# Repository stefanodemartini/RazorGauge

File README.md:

# RazorGauge

RazorGauge is a line-diameter measurement and fly-line design project. This repository contains
the firmware, Windows desktop application, shared physics library, CLI, and the hardware design
files.

## Repository map

| Path | Purpose |
|---|---|
| `master/` | Active ESP32 master firmware (0.4.25-RB2, caliper-based) |
| `slave/` | Active ESP32-classic motor controller firmware (0.6.8, Wi-Fi/RX2 diagnostics) |
| `master_razorgauge/` | Preliminary optical RazorGauge master (1.0.4-alpha) |
| `gauge_esp32/`, `gauge_esp32s3/`, `encoder_test/` | Bench and diagnostic firmware |
| `app/` | Windows WPF desktop application |
| `FlyLinePhysics/` | Shared line-physics and `.flp` serialization library |
| `FlyLinePhysics.Tests/` | Unit tests for the shared library |
| `cli/` | `flyline` command-line design and analysis tool |
| `cad/`, `integrazione_profiler/`, `piastra_alluminio/` | Mechanical CAD and integration design |
| `scheda/`, `scheda_smd/` | RazorBoard KiCad projects |
| `strumenti/` | Build, simulation, and verification scripts |

Generated outputs (such as mesh files, renders, PDFs, and build products) are generally excluded
from version control; the corresponding source files and scripts are kept in the repository.

## Where to start

- [FIRMWARE.md](./FIRMWARE.md): canonical sketches, active versions, boards, and firmware notes.
- [MANUALE.md](./MANUALE.md): application workflow and user-facing behavior.
- [STATO_PROGETTO.md](./STATO_PROGETTO.md): authoritative hardware decisions and current project status.
- [CONTEXT.md](./CONTEXT.md): software/repository context.
- [app/README.md](./app/README.md): desktop application overview.

## Build and test the .NET projects

From the repository root:

```powershell
dotnet build app\app.sln
dotnet test FlyLinePhysics.Tests\FlyLinePhysics.Tests.csproj
dotnet build cli\FlyLineCli.csproj
```

Run the desktop app with `dotnet run --project app\DiametroLineaDesktop.csproj`. The CLI project
is Windows-targeted because it currently references the WPF application for shared design and
export services.

## Arduino firmware

Build and flash each sketch for its matching board using Arduino IDE or `arduino-cli`. The active
motor slave targets the classic ESP32; do not select ESP32-S3 for `slave/slave.ino`. See
[FIRMWARE.md](./FIRMWARE.md) for the current board/version matrix and flash guidance.

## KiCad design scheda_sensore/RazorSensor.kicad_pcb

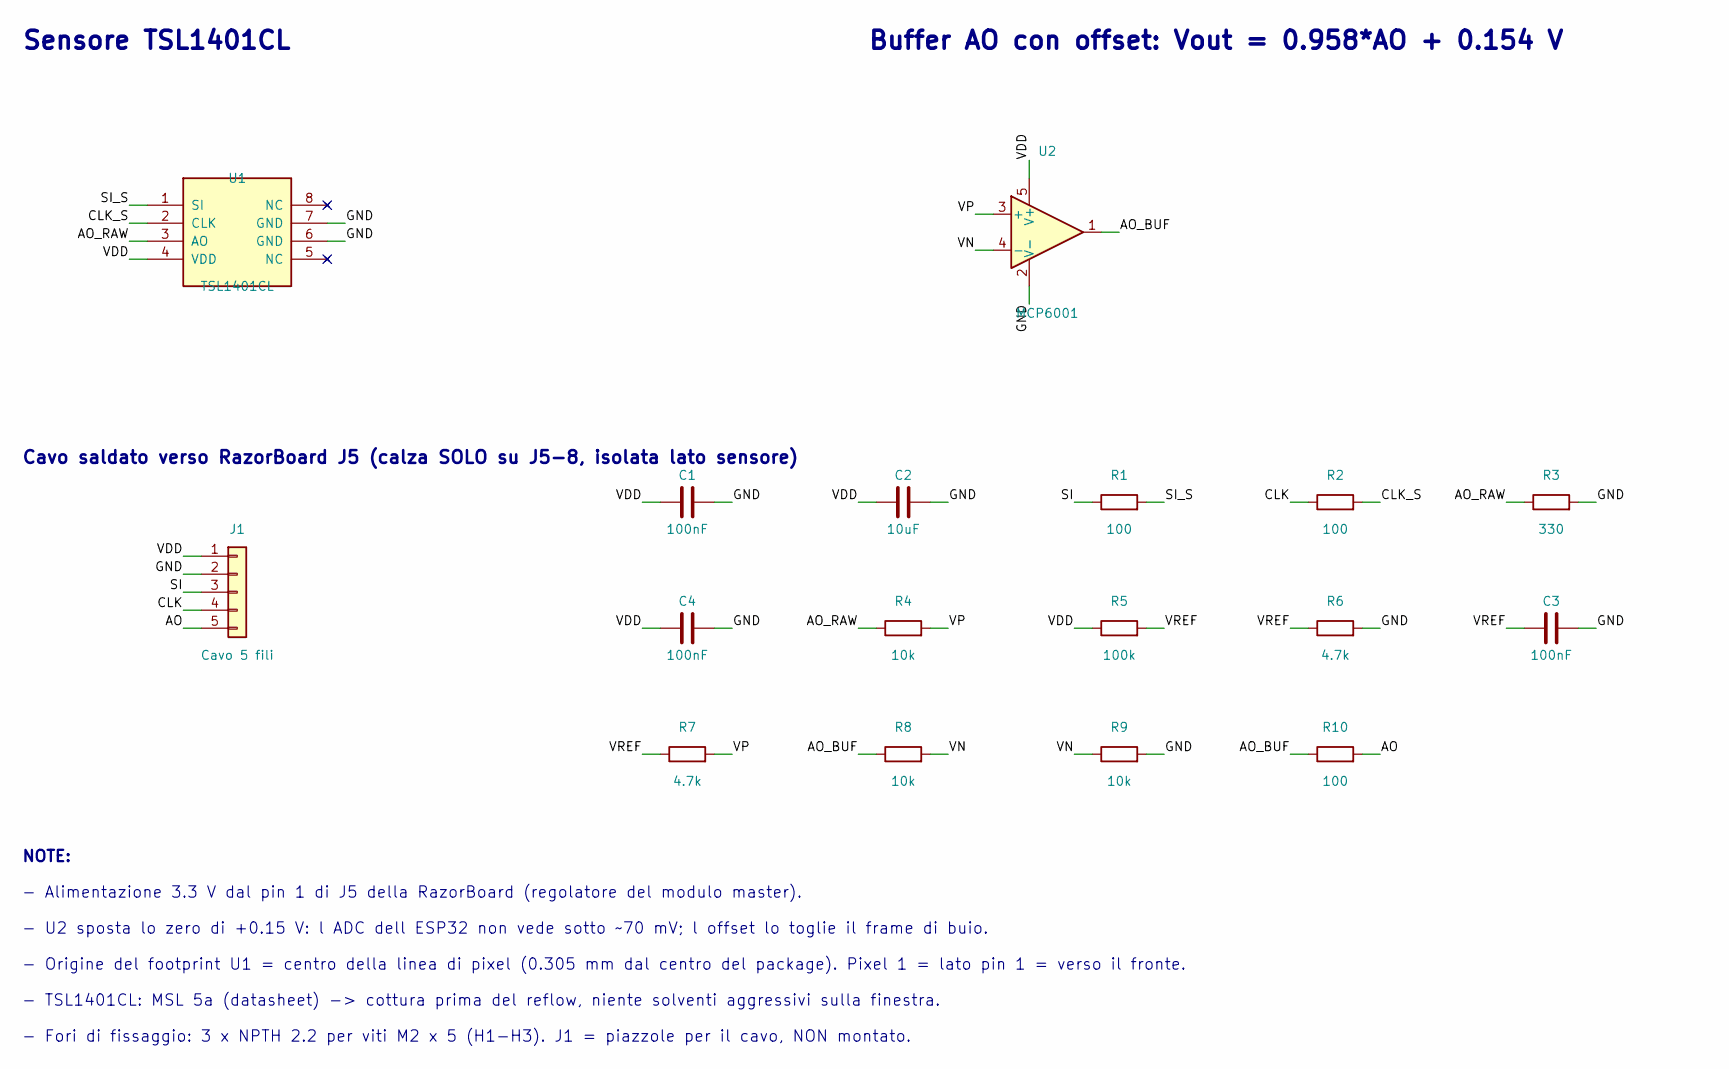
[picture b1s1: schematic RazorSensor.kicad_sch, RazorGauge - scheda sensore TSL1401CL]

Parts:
C1, C3, C4: 100nF; C_0603_1608Metric; MPN CC0603KRX7R9BB104 50V; LCSC C14663
C2: 10uF; C_0805_2012Metric; MPN CL21A106KAYNNNE 25V; LCSC C15850
J1: Cavo 5 fili; PinHeader_1x05_P2.00mm_Vertical; MPN piazzole per saldare il cavo: 1 3V3 / 2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
R1, R2, R10: 100; R_0603_1608Metric; MPN 0603WAF1000T5E; LCSC C22775
R3: 330; R_0603_1608Metric; MPN 0603WAF3300T5E; LCSC C23138
R4, R8, R9: 10k; R_0603_1608Metric; MPN 0603WAF1002T5E; LCSC C25804
R5: 100k; R_0603_1608Metric; MPN 0603WAF1003T5E; LCSC C25803
R6, R7: 4.7k; R_0603_1608Metric; MPN 0603WAF4701T5E; LCSC C23162
U1: TSL1401CL; TSL1401CL_ams_CL; MPN ams TSL1401CL (128x1, package CL, MSL 5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; LCSC C2802316
U2: MCP6001; SOT-23-5; MPN Microchip MCP6001T-I/OT (rail-to-rail i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; LCSC C116490

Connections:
AO: J1.5, R10.2
AO_BUF: R8.1, R10.1, U2.1
AO_RAW: R3.1, R4.1, U1.3 (AO)
CLK: J1.4, R2.1
CLK_S: R2.2, U1.2 (CLK)
GND: C1.2, C2.2, C3.2, C4.2, J1.2, R3.2, R6.2, R9.2, U1.6 (GND), U1.7 (GND), U2.2 (V-)
SI: J1.3, R1.1
SI_S: R1.2, U1.1 (SI)
VDD: C1.1, C2.1, C4.1, J1.1, R5.1, U1.4 (VDD), U2.5 (V+)
VN: R8.2, R9.1, U2.4 (-)
VP: R4.2, R7.2, U2.3 (+)
VREF: C3.1, R5.2, R6.1, R7.1

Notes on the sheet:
Sensore TSL1401CL
Cavo saldato verso RazorBoard J5 (calza SOLO su J5-8, isolata lato sensore)
Buffer AO con offset: Vout = 0.958*AO + 0.154 V
NOTE:
- Alimentazione 3.3 V dal pin 1 di J5 della RazorBoard (regolatore del modulo master).
- U2 sposta lo zero di +0.15 V: l ADC dell ESP32 non vede sotto ~70 mV; l offset lo toglie il frame di buio.
- Origine del footprint U1 = centro della linea di pixel (0.305 mm dal centro del package). Pixel 1 = lato pin 1 = verso il fronte.
- TSL1401CL: MSL 5a (datasheet) -> cottura prima del reflow, niente solventi aggressivi sulla finestra.
- Fori di fissaggio: 3 x NPTH 2.2 per viti M2 x 5 (H1-H3). J1 = piazzole per il cavo, NON montato.

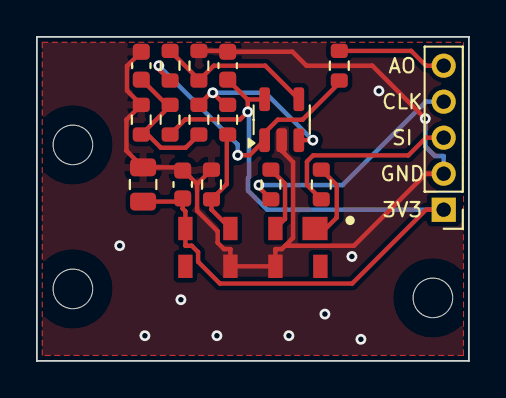
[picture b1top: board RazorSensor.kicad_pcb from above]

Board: 2 copper layers, 24.0 x 18.0 mm, 20 parts (0 on the bottom side), 12 nets.

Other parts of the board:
H1, H2, H3: M2; MountingHole_2.2mm_M2

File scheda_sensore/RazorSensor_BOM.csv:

Rif;Valore;Footprint;Codice / note;LCSC
U1;TSL1401CL;TSL1401CL_ams_CL;ams TSL1401CL (128x1, package CL, MSL 5a da datasheet);C2802316
C1;100nF;C_0603_1608Metric;CC0603KRX7R9BB104 50V;C14663
C2;10uF;C_0805_2012Metric;CL21A106KAYNNNE 25V;C15850
R1;100;R_0603_1608Metric;0603WAF1000T5E;C22775
R2;100;R_0603_1608Metric;0603WAF1000T5E;C22775
R3;330;R_0603_1608Metric;0603WAF3300T5E;C23138
U2;MCP6001;SOT-23-5;Microchip MCP6001T-I/OT (rail-to-rail in/out, 1 MHz, 0.6 V/us) - NON LMV321/MCP6001R/MCP6001U;C116490
C4;100nF;C_0603_1608Metric;CC0603KRX7R9BB104 50V;C14663
R4;10k;R_0603_1608Metric;0603WAF1002T5E;C25804
R5;100k;R_0603_1608Metric;0603WAF1003T5E;C25803
R6;4.7k;R_0603_1608Metric;0603WAF4701T5E;C23162
C3;100nF;C_0603_1608Metric;CC0603KRX7R9BB104 50V;C14663
R7;4.7k;R_0603_1608Metric;0603WAF4701T5E;C23162
R8;10k;R_0603_1608Metric;0603WAF1002T5E;C25804
R9;10k;R_0603_1608Metric;0603WAF1002T5E;C25804
R10;100;R_0603_1608Metric;0603WAF1000T5E;C22775
J1;Cavo 5 fili;PinHeader_1x05_P2.00mm_Vertical;"piazzole per saldare il cavo: 1 3V3 / 2 GND / 3 SI / 4 CLK / 5 AO (= J5 pin 1-5; calza solo su J5-8) - NON MONTARE";

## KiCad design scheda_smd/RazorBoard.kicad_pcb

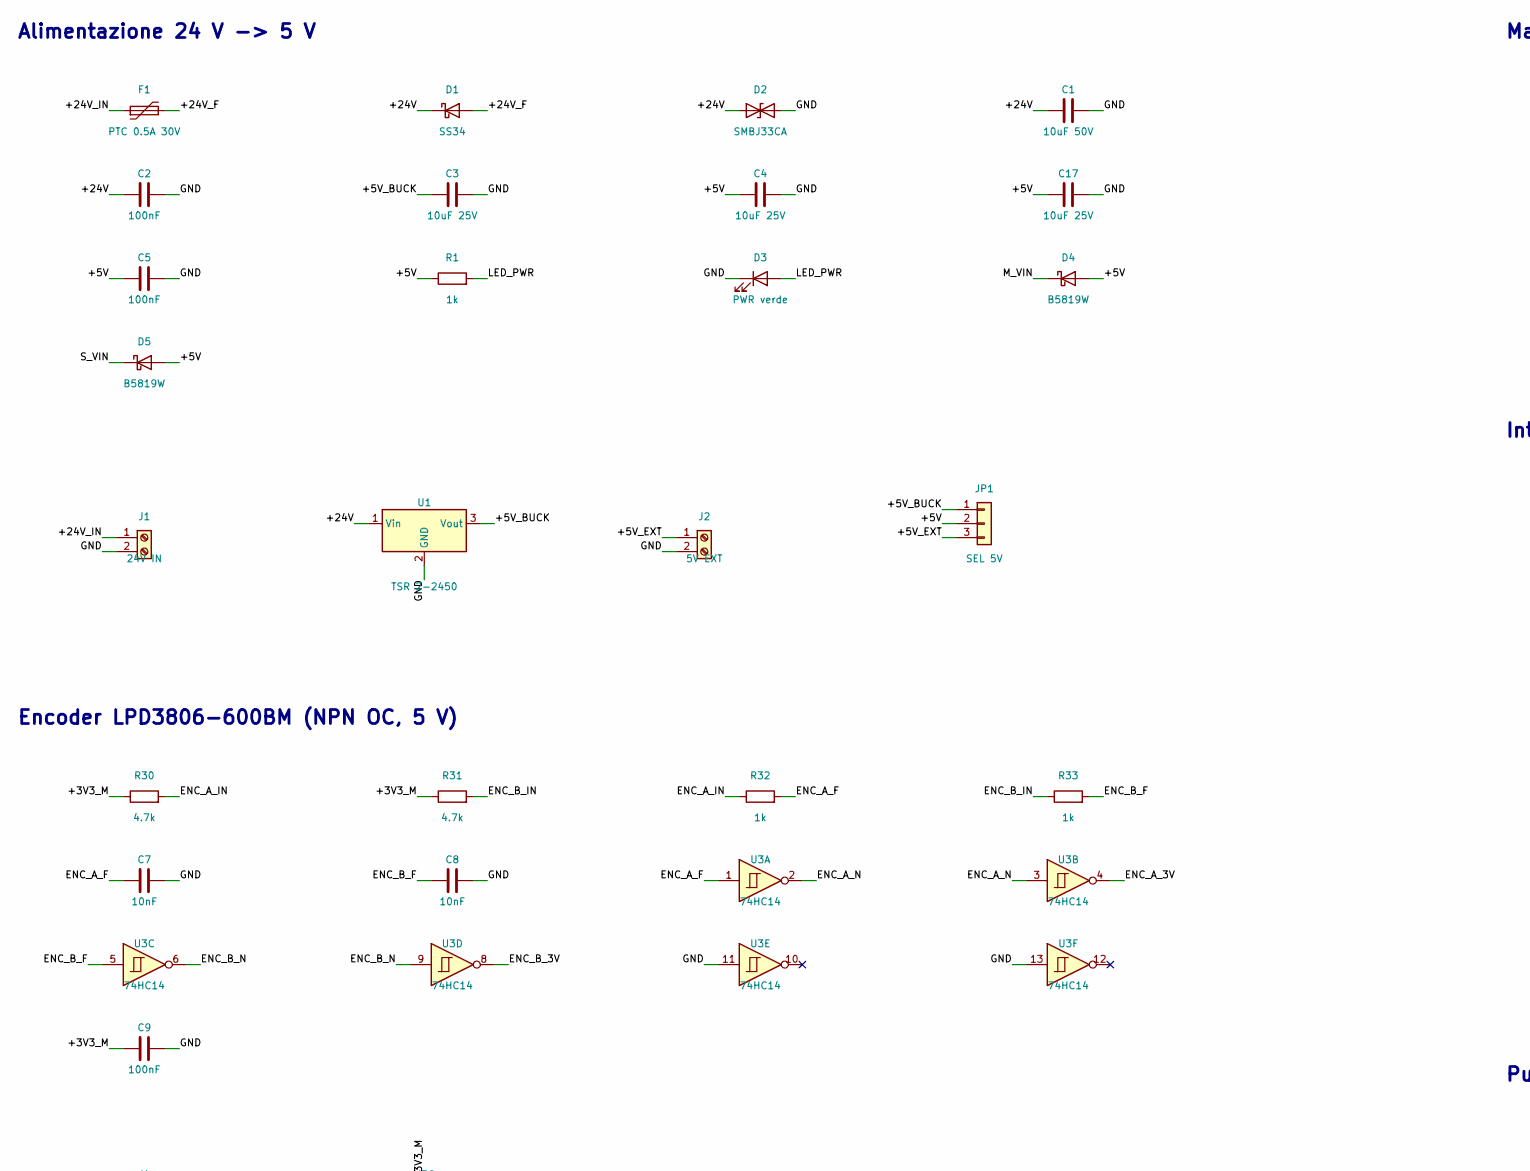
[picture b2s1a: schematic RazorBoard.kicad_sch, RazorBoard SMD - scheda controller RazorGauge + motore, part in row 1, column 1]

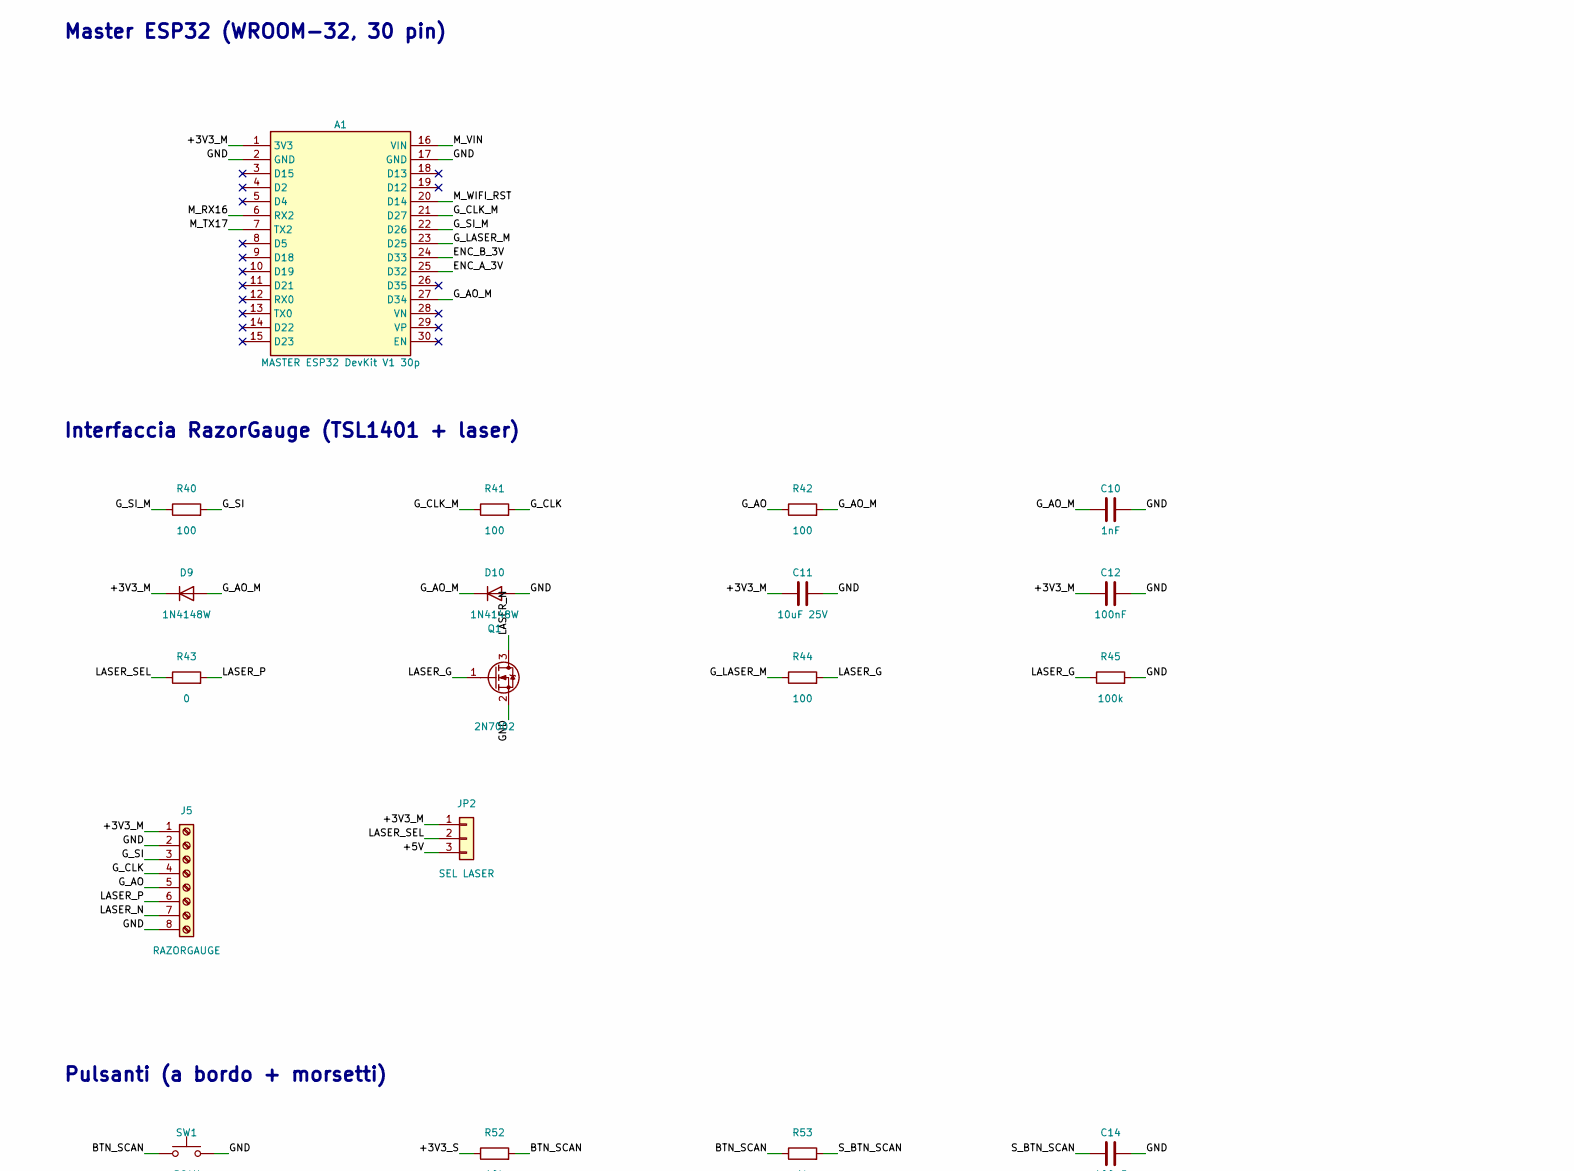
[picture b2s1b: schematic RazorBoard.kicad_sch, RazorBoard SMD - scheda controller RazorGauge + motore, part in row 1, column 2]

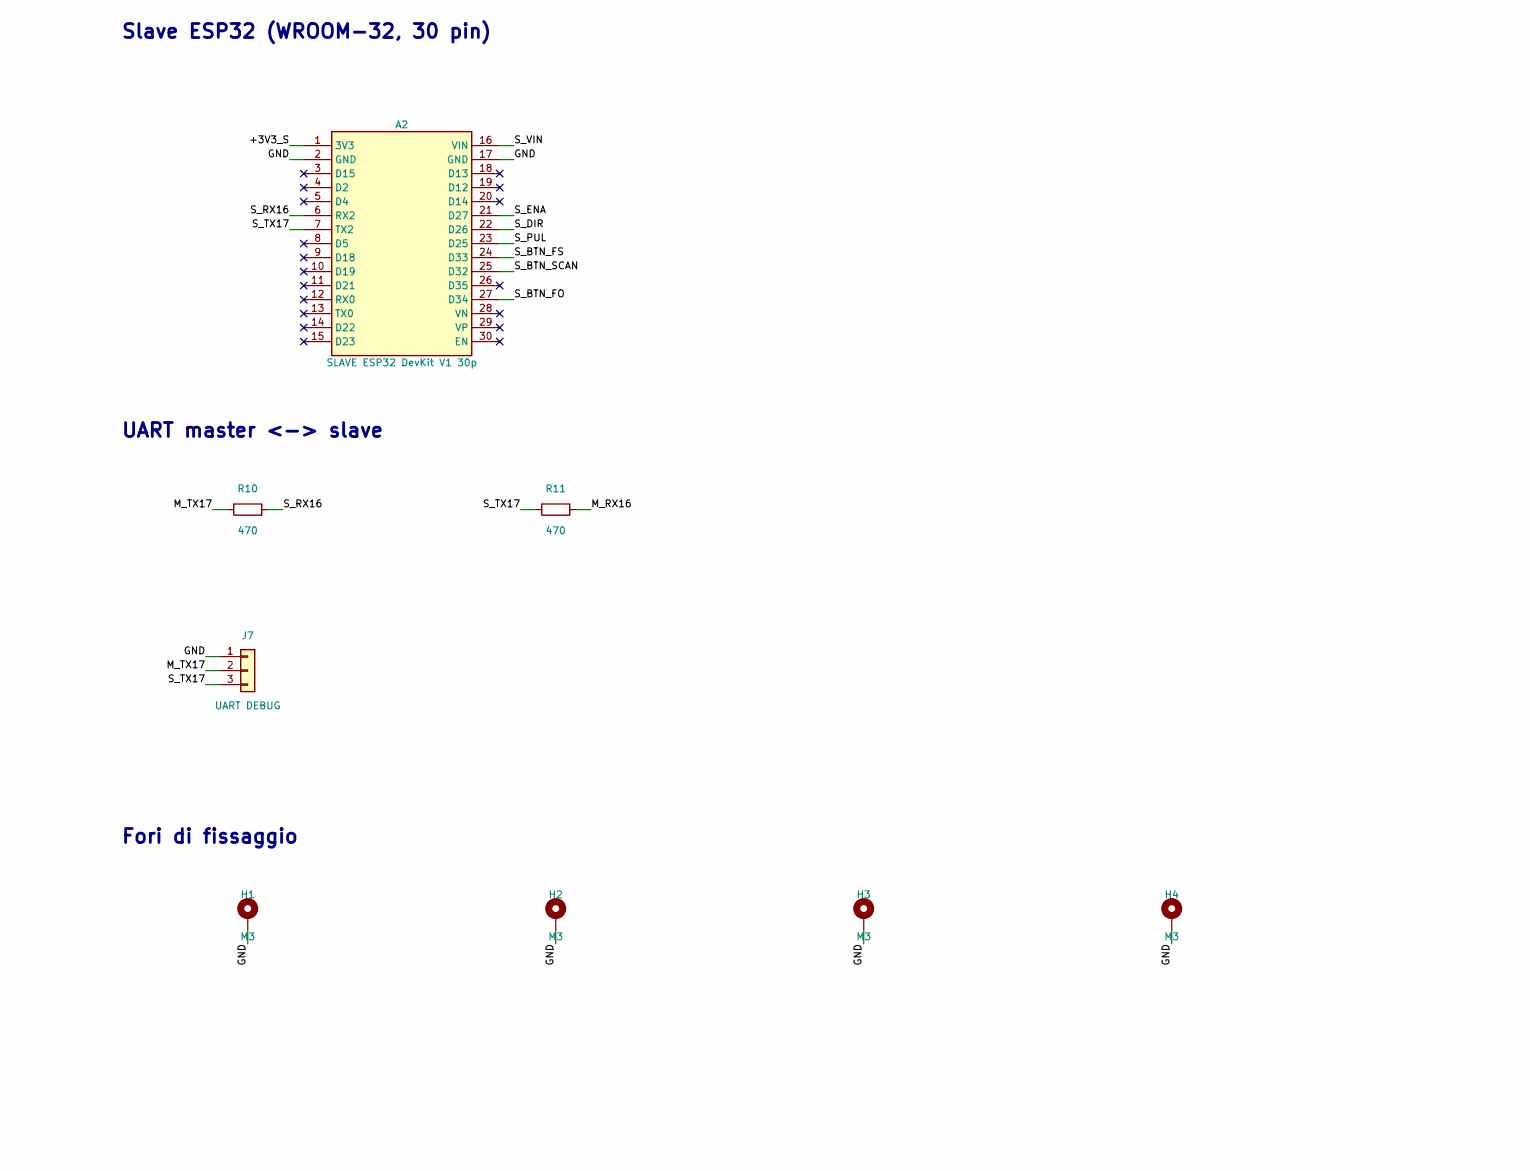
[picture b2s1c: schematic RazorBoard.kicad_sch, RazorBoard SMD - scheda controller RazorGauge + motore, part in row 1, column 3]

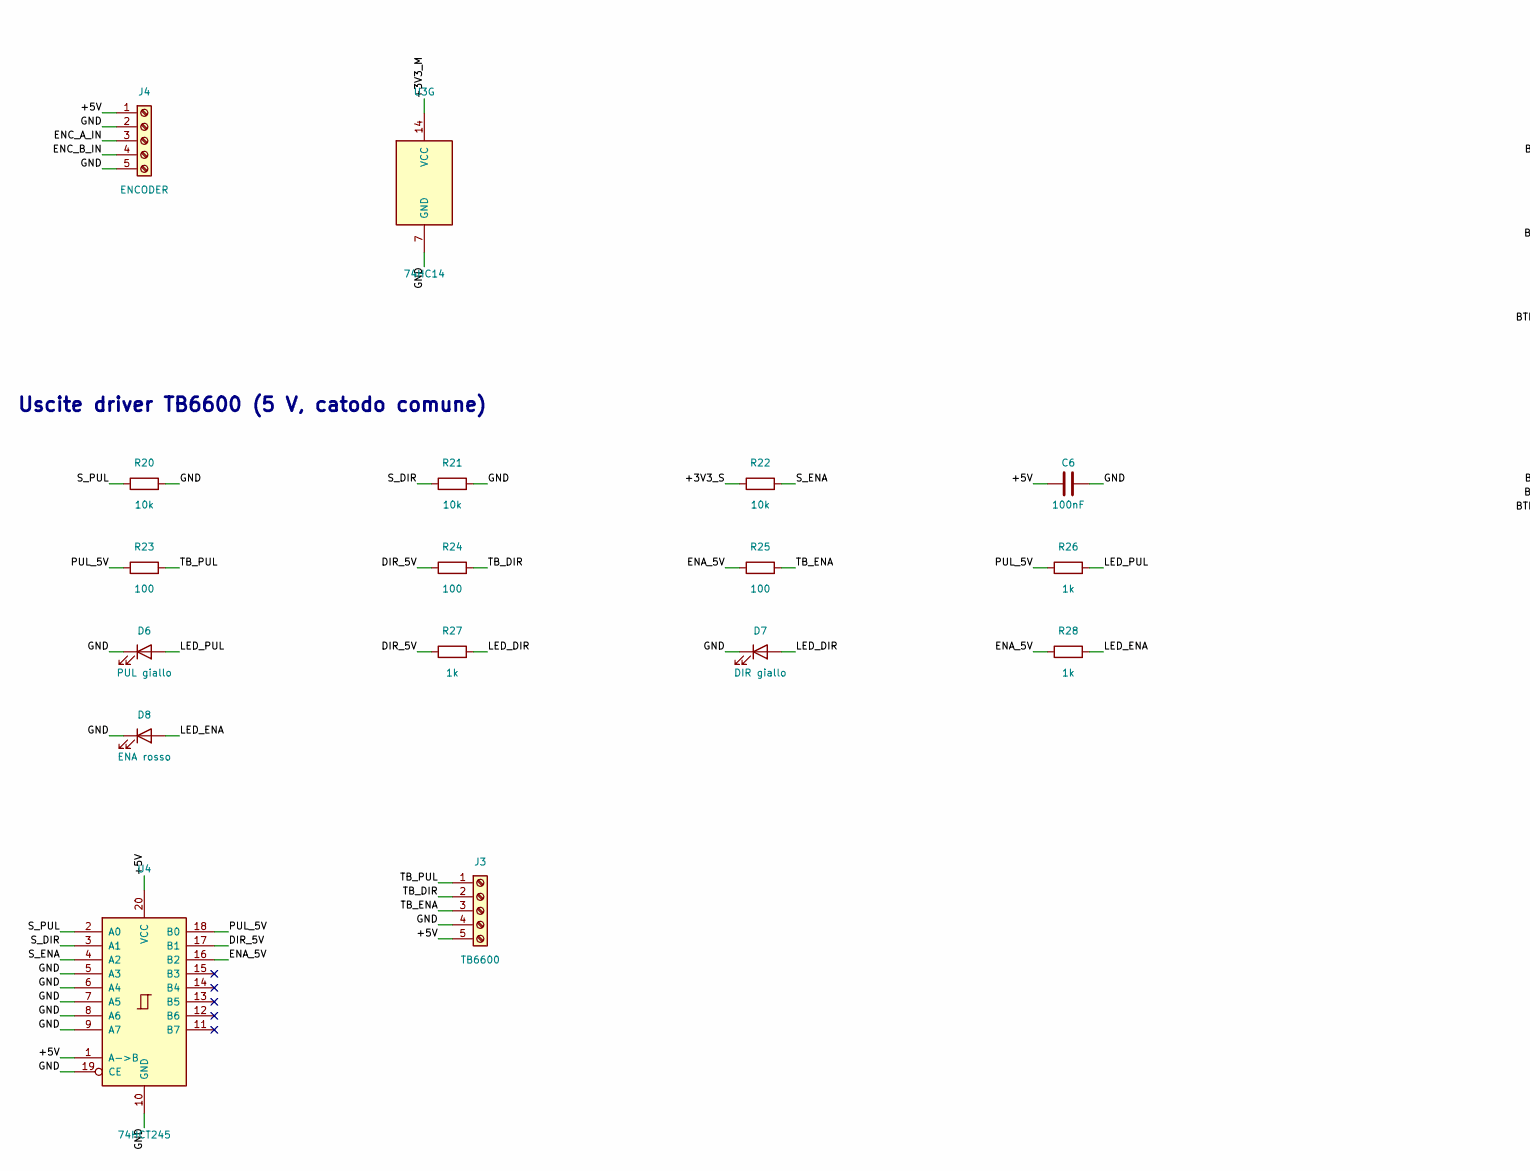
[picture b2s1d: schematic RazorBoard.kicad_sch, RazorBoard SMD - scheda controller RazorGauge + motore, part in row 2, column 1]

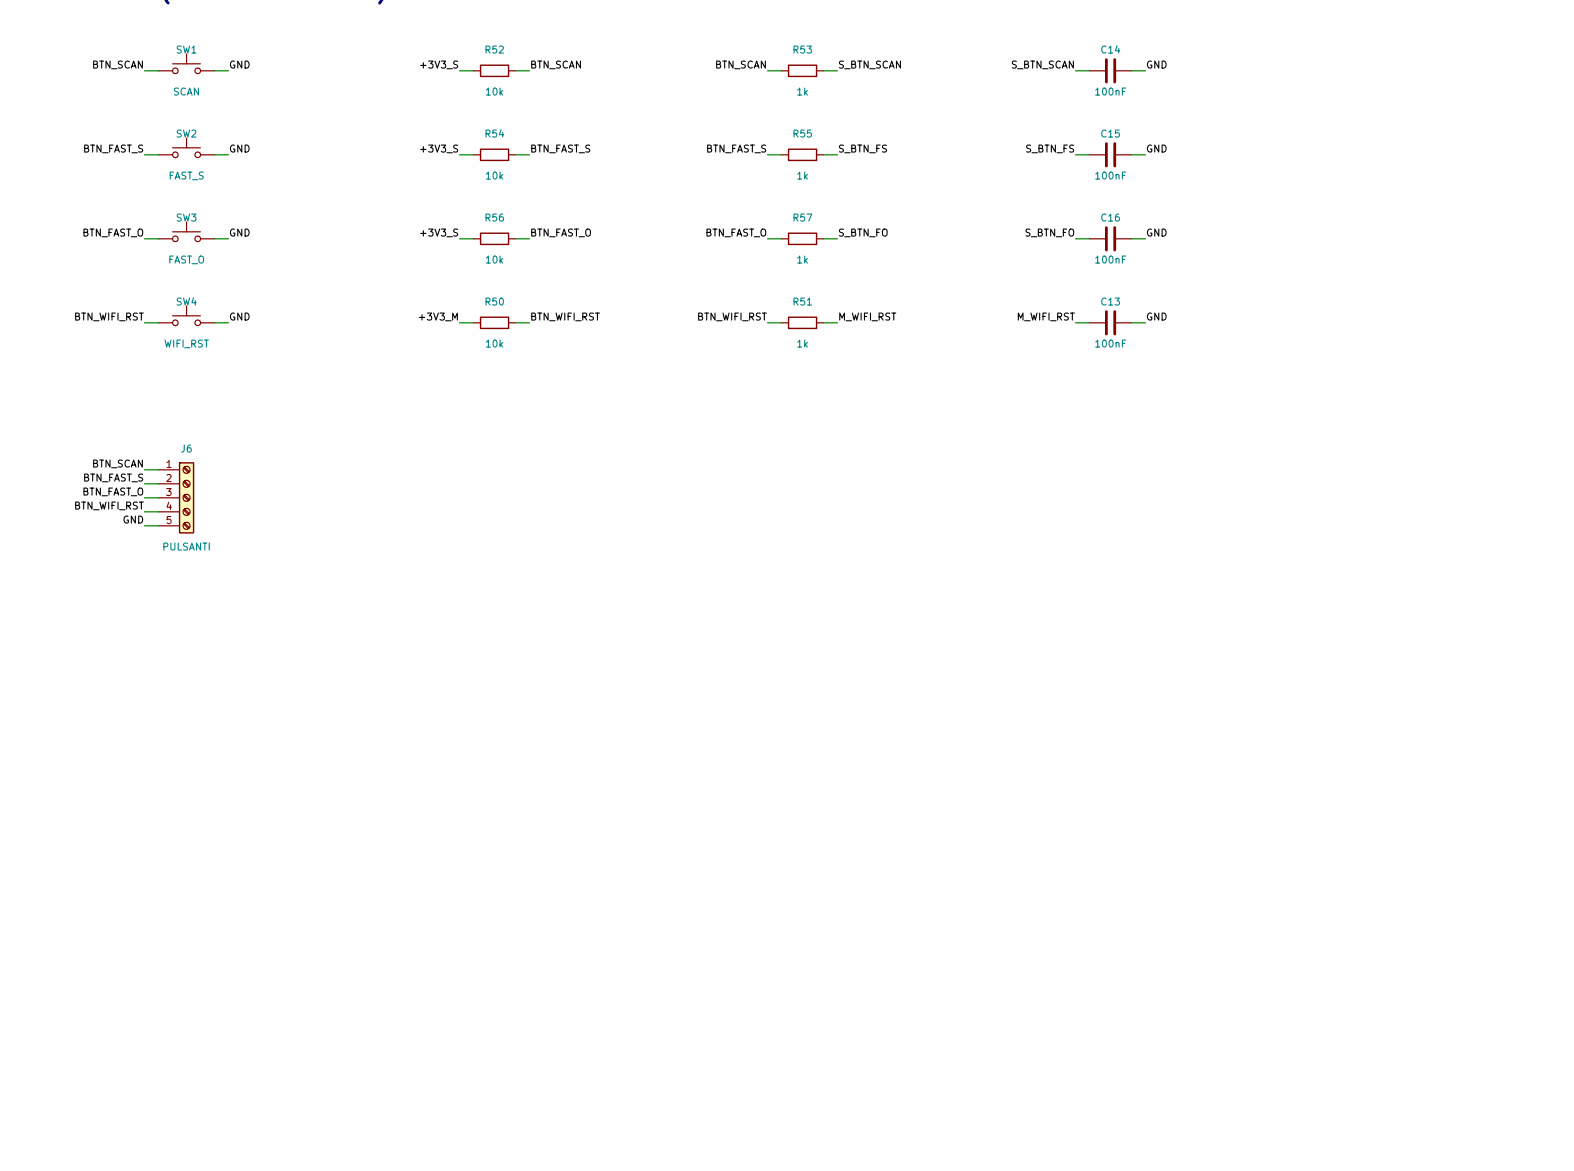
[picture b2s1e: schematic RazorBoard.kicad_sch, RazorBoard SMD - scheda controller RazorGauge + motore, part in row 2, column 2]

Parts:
A1: MASTER ESP32 DevKit V1 30p; ESP32_DevKitV1_30p_W25.4; MPN 2x zoccolo femmina 1x15 passo 2.54, fil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
A2: SLAVE ESP32 DevKit V1 30p; ESP32_DevKitV1_30p_W25.4; MPN 2x zoccolo femmina 1x15 passo 2.54, fil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
C1: 10uF 50V; C_1206_3216Metric; MPN CL31A106KBHNNNE; LCSC C13585
C2, C5, C6, C9, C12, C13, C14, C15, C16: 100nF; C_0603_1608Metric; MPN CC0603KRX7R9BB104 50V; LCSC C14663
C3, C4, C11, C17: 10uF 25V; C_0805_2012Metric; MPN CL21A106KAYNNNE; LCSC C15850
C7, C8: 10nF; C_0603_1608Metric; MPN 0603B103K500NT 50V; LCSC C57112
C10: 1nF; C_0603_1608Metric; MPN CL10B102KB8NNNC 50V; LCSC C1588
D1: SS34; D_SMA; MPN SS34 3A 40V; LCSC C8678
D2: SMBJ33CA; D_SMB; MPN SMBJ33CA; LCSC C492017
D3: PWR verde; LED_0603_1608Metric; MPN KT-0603G; LCSC C12624
D4: B5819W; D_SOD-123; MPN B5819W SL (blocca ritorno da USB master); LCSC C8598
D5: B5819W; D_SOD-123; MPN B5819W SL (blocca ritorno da USB slave); LCSC C8598
D6: PUL giallo; LED_0603_1608Metric; MPN KT-0603Y; LCSC C2287
D7: DIR giallo; LED_0603_1608Metric; MPN KT-0603Y; LCSC C2287
D8: ENA rosso; LED_0603_1608Metric; MPN KT-0603R; LCSC C2286
D9, D10: 1N4148W; D_SOD-123; MPN 1N4148W; LCSC C81598
F1: PTC 0.5A 30V; Fuse_1812_4532Metric; MPN SMD1812P050TF/30 (hold 0.5A, trip 1A); LCSC C12559
H1, H2, H3, H4: M3; MountingHole_3.2mm_M3_Pad
J1: 24V IN; TerminalBlock_Phoenix_MKDS-1,5-2-5.08_1x02_P5.08mm_Horizont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
J2: 5V EXT; TerminalBlock_Phoenix_MKDS-1,5-2-5.08_1x02_P5.08mm_Horizont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
J3: TB6600; TerminalBlock_Phoenix_MKDS-1,5-5-5.08_1x05_P5.08mm_Horizont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; MPN PUL->PUL+, DIR->DIR+, ENA->ENA+, GND->P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
J4: ENCODER; TerminalBlock_Phoenix_MKDS-1,5-5-5.08_1x05_P5.08mm_Horizont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; MPN rosso +5V, nero GND, verde A, bianco B,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
J5: RAZORGAUGE; TerminalBlock_Phoenix_MKDS-1,5-8-5.08_1x08_P5.08mm_Horizont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; MPN cavo schermato max 50 cm, calza al pin 8
J6: PULSANTI; TerminalBlock_Phoenix_MKDS-1,5-5-5.08_1x05_P5.08mm_Horizont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
J7: UART DEBUG; PinHeader_1x03_P2.54mm_Vertical
JP1: SEL 5V; PinHeader_1x03_P2.54mm_Vertical; MPN Header 3 pin + jumper (1-2 = convertito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
JP2: SEL LASER; PinHeader_1x03_P2.54mm_Vertical; MPN Header 3 pin + jumper (1-2 = laser a 3.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
Q1: 2N7002; SOT-23; MPN 2N7002 (60V 115mA); LCSC C8545
R1, R26, R27, R28, R32, R33, R51, R53, R55, R57: 1k; R_0603_1608Metric; MPN 0603WAF1001T5E; LCSC C21190
R10, R11: 470; R_0603_1608Metric; MPN 0603WAF4700T5E; LCSC C23179
R20, R21, R22, R50, R52, R54, R56: 10k; R_0603_1608Metric; MPN 0603WAF1002T5E; LCSC C25804
R23, R24, R25, R40, R41, R42, R44: 100; R_0603_1608Metric; MPN 0603WAF1000T5E; LCSC C22775
R30, R31: 4.7k; R_0603_1608Metric; MPN 0603WAF4701T5E; LCSC C23162
R43: 0; R_0603_1608Metric; MPN 0603WAF0000T5E; LCSC C21189
R45: 100k; R_0603_1608Metric; MPN 0603WAF1003T5E; LCSC C25803
SW1: SCAN; SW_PUSH_6mm
SW2: FAST_S; SW_PUSH_6mm
SW3: FAST_O; SW_PUSH_6mm
SW4: WIFI_RST; SW_PUSH_6mm
U1: TSR 2-2450; Converter_DCDC_TRACO_TSR-1_THT; MPN Traco TSR 2-2450 (5V 2A)
U3: 74HC14; SOIC-14_3.9x8.7mm_P1.27mm; MPN 74HC14D,653 (a 3.3V, doppia inversione); LCSC C5605
U4: 74HCT245; SOIC-20W_7.5x12.8mm_P1.27mm; MPN 74HCT245D,653 (ingressi TTL, uscite 5V); LCSC C5979

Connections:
+3V3_M: A1.1 (3V3), C9.1, C11.1, C12.1, D9.1 (K), J5.1, JP2.1, R30.1, R31.1, R50.1, U3.14 (VCC)
+3V3_S: A2.1 (3V3), R22.1, R52.1, R54.1, R56.1
+5V: C4.1, C5.1, C6.1, C17.1, D4.2 (A), D5.2 (A), J3.5, J4.1, JP1.2, JP2.3, R1.1, U4.1 (A->B), U4.20 (VCC)
+5V_BUCK: C3.1, JP1.1, U1.3 (Vout)
+5V_EXT: J2.1, JP1.3
+24V: C1.1, C2.1, D1.1 (K), D2.1 (A1), U1.1 (Vin)
+24V_F: D1.2 (A), F1.2
+24V_IN: F1.1, J1.1
BTN_FAST_O: J6.3, R56.2, R57.1, SW3.1
BTN_FAST_S: J6.2, R54.2, R55.1, SW2.1
BTN_SCAN: J6.1, R52.2, R53.1, SW1.1
BTN_WIFI_RST: J6.4, R50.2, R51.1, SW4.1
DIR_5V: R24.1, R27.1, U4.17 (B1)
ENA_5V: R25.1, R28.1, U4.16 (B2)
ENC_A_3V: A1.25 (D32), U3.4
ENC_A_F: C7.1, R32.2, U3.1
ENC_A_IN: J4.3, R30.2, R32.1
ENC_A_N: U3.2, U3.3
ENC_B_3V: A1.24 (D33), U3.8
ENC_B_F: C8.1, R33.2, U3.5
ENC_B_IN: J4.4, R31.2, R33.1
ENC_B_N: U3.6, U3.9
GND: A1.2 (GND), A1.17 (GND), A2.2 (GND), A2.17 (GND), C1.2, C2.2, C3.2, C4.2, C5.2, C6.2, C7.2, C8.2, C9.2, C10.2, C11.2, C12.2, C13.2, C14.2, C15.2, C16.2, C17.2, D2.2 (A2), D3.1 (K), D6.1 (K), D7.1 (K), D8.1 (K), D10.2 (A), H1.1, H2.1, H3.1, H4.1, J1.2, J2.2, J3.4, J4.2, J4.5, J5.2, J5.8, J6.5, J7.1, Q1.2 (S), R20.2, R21.2, R45.2, SW1.2, SW2.2, SW3.2, SW4.2, U1.2 (GND), U3.7 (GND), U3.11, U3.13, U4.5 (A3), U4.6 (A4), U4.7 (A5), U4.8 (A6), U4.9 (A7), U4.10 (GND), U4.19 (CE)
G_AO: J5.5, R42.1
G_AO_M: A1.27 (D34), C10.1, D9.2 (A), D10.1 (K), R42.2
G_CLK: J5.4, R41.2
G_CLK_M: A1.21 (D27), R41.1
G_LASER_M: A1.23 (D25), R44.1
G_SI: J5.3, R40.2
G_SI_M: A1.22 (D26), R40.1
LASER_G: Q1.1 (G), R44.2, R45.1
LASER_N: J5.7, Q1.3 (D)
LASER_P: J5.6, R43.2
LASER_SEL: JP2.2, R43.1
LED_DIR: D7.2 (A), R27.2
LED_ENA: D8.2 (A), R28.2
LED_PUL: D6.2 (A), R26.2
LED_PWR: D3.2 (A), R1.2
M_RX16: A1.6 (RX2), R11.2
M_TX17: A1.7 (TX2), J7.2, R10.1
M_VIN: A1.16 (VIN), D4.1 (K)
M_WIFI_RST: A1.20 (D14), C13.1, R51.2
PUL_5V: R23.1, R26.1, U4.18 (B0)
S_BTN_FO: A2.27 (D34), C16.1, R57.2
S_BTN_FS: A2.24 (D33), C15.1, R55.2
S_BTN_SCAN: A2.25 (D32), C14.1, R53.2
S_DIR: A2.22 (D26), R21.1, U4.3 (A1)
S_ENA: A2.21 (D27), R22.2, U4.4 (A2)
S_PUL: A2.23 (D25), R20.1, U4.2 (A0)
S_RX16: A2.6 (RX2), R10.2
S_TX17: A2.7 (TX2), J7.3, R11.1
S_VIN: A2.16 (VIN), D5.1 (K)
TB_DIR: J3.2, R24.2
TB_ENA: J3.3, R25.2
TB_PUL: J3.1, R23.2

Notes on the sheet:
Alimentazione 24 V -> 5 V
Encoder LPD3806-600BM (NPN OC, 5 V)
Uscite driver TB6600 (5 V, catodo comune)
Master ESP32 (WROOM-32, 30 pin)
Interfaccia RazorGauge (TSL1401 + laser)
Pulsanti (a bordo + morsetti)
Slave ESP32 (WROOM-32, 30 pin)
UART master <-> slave
Fori di fissaggio
NOTE:
- Encoder spostato da GPIO12/13 a GPIO32/33 (GPIO12 e pin di avvio): aggiornare ENCODER_DATA_PIN=32, ENCODER_CLOCK_PIN=33 nel master.
- TB6600 a catodo comune: PUL/DIR/ENA alti = LED opto acceso. ENA alto = motore libero (pull-up R22 = motore libero all accensione).
- Il motore e il TB6600 si alimentano direttamente dall alimentatore 24 V, non dalla scheda.
- Slave = ESP32 DevKit V1 30p come il master: PUL/DIR/ENA su GPIO25/26/27, pulsanti su GPIO32/33/34, UART su GPIO16/17 (firmware slave 0.6.0).
- D4/D5 impediscono che l USB di un modulo alimenti tutta la scheda.
- Calza dei cavi schermati collegata a GND solo lato scheda.

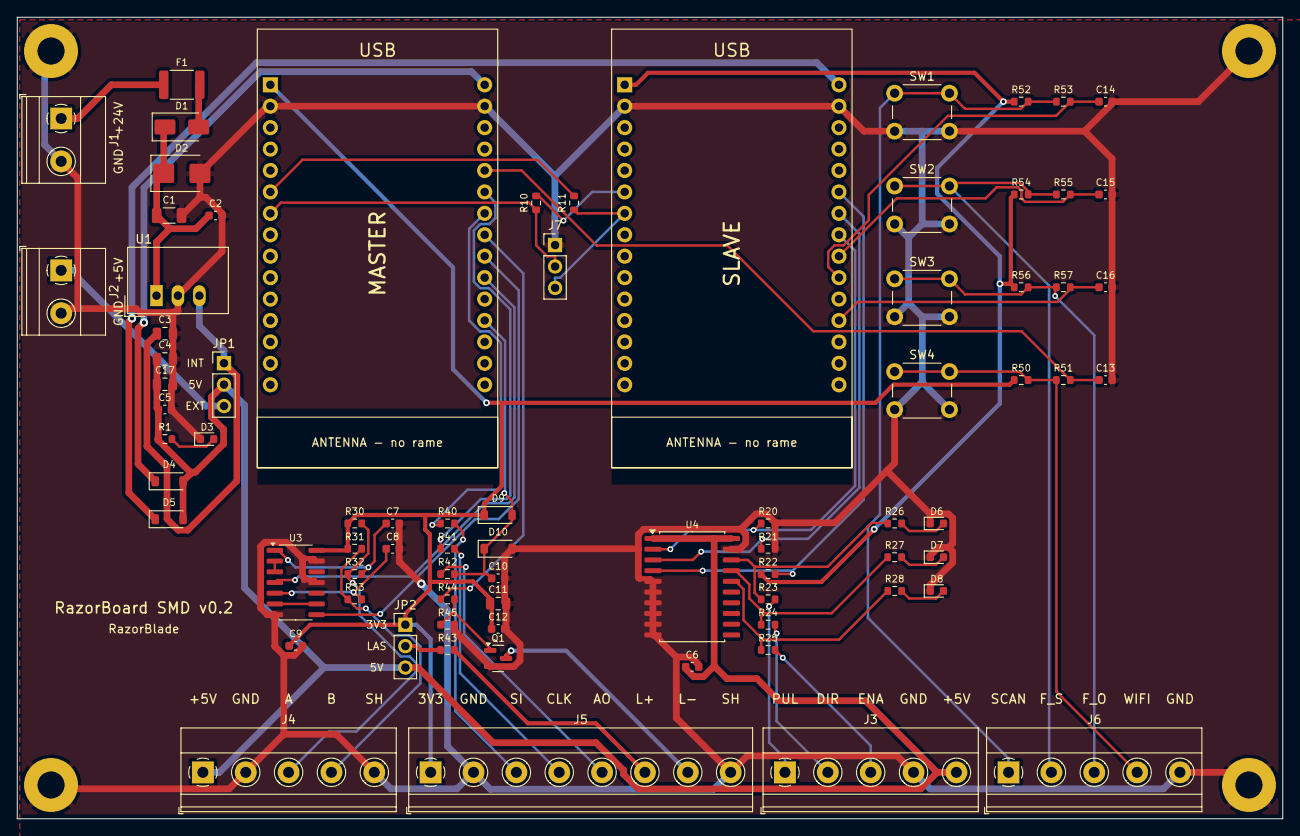
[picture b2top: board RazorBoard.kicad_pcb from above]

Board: 2 copper layers, 150.0 x 95.0 mm, 81 parts (0 on the bottom side), 55 nets.

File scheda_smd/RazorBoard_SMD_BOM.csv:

Rif;Valore;Footprint;Codice / note;LCSC;Montaggio
J1;24V IN;TerminalBlock_Phoenix_MKDS-1,5-2-5.08_1x02_P5.08mm_Horizontal;;;a mano (THT)
F1;PTC 0.5A 30V;Fuse_1812_4532Metric;SMD1812P050TF/30 (hold 0.5A, trip 1A);C12559;fabbrica (SMT)
D1;SS34;D_SMA;SS34 3A 40V;C8678;fabbrica (SMT)
D2;SMBJ33CA;D_SMB;SMBJ33CA;C492017;fabbrica (SMT)
C1;10uF 50V;C_1206_3216Metric;CL31A106KBHNNNE;C13585;fabbrica (SMT)
C2;100nF;C_0603_1608Metric;CC0603KRX7R9BB104 50V;C14663;fabbrica (SMT)
U1;TSR 2-2450;Converter_DCDC_TRACO_TSR-1_THT;Traco TSR 2-2450 (5V 2A);;a mano (THT)
C3;10uF 25V;C_0805_2012Metric;CL21A106KAYNNNE;C15850;fabbrica (SMT)
J2;5V EXT;TerminalBlock_Phoenix_MKDS-1,5-2-5.08_1x02_P5.08mm_Horizontal;;;a mano (THT)
JP1;SEL 5V;PinHeader_1x03_P2.54mm_Vertical;Header 3 pin + jumper (1-2 = convertitore interno, 2-3 = 5V esterno);;a mano (THT)
C4;10uF 25V;C_0805_2012Metric;CL21A106KAYNNNE;C15850;fabbrica (SMT)
C17;10uF 25V;C_0805_2012Metric;CL21A106KAYNNNE;C15850;fabbrica (SMT)
C5;100nF;C_0603_1608Metric;CC0603KRX7R9BB104 50V;C14663;fabbrica (SMT)
R1;1k;R_0603_1608Metric;0603WAF1001T5E;C21190;fabbrica (SMT)
D3;PWR verde;LED_0603_1608Metric;KT-0603G;C12624;fabbrica (SMT)
D4;B5819W;D_SOD-123;B5819W SL (blocca ritorno da USB master);C8598;fabbrica (SMT)
D5;B5819W;D_SOD-123;B5819W SL (blocca ritorno da USB slave);C8598;fabbrica (SMT)
A1;MASTER ESP32 DevKit V1 30p;ESP32_DevKitV1_30p_W25.4;2x zoccolo femmina 1x15 passo 2.54, file a 25.4 mm;;a mano (THT)
A2;SLAVE ESP32 DevKit V1 30p;ESP32_DevKitV1_30p_W25.4;2x zoccolo femmina 1x15 passo 2.54, file a 25.4 mm;;a mano (THT)
R10;470;R_0603_1608Metric;0603WAF4700T5E;C23179;fabbrica (SMT)
R11;470;R_0603_1608Metric;0603WAF4700T5E;C23179;fabbrica (SMT)
J7;UART DEBUG;PinHeader_1x03_P2.54mm_Vertical;;;a mano (THT)
J4;ENCODER;TerminalBlock_Phoenix_MKDS-1,5-5-5.08_1x05_P5.08mm_Horizontal;rosso +5V, nero GND, verde A, bianco B, calza GND;;a mano (THT)
R30;4.7k;R_0603_1608Metric;0603WAF4701T5E;C23162;fabbrica (SMT)
R31;4.7k;R_0603_1608Metric;0603WAF4701T5E;C23162;fabbrica (SMT)
R32;1k;R_0603_1608Metric;0603WAF1001T5E;C21190;fabbrica (SMT)
R33;1k;R_0603_1608Metric;0603WAF1001T5E;C21190;fabbrica (SMT)
C7;10nF;C_0603_1608Metric;0603B103K500NT 50V;C57112;fabbrica (SMT)
C8;10nF;C_0603_1608Metric;0603B103K500NT 50V;C57112;fabbrica (SMT)
U3;74HC14;SOIC-14_3.9x8.7mm_P1.27mm;74HC14D,653 (a 3.3V, doppia inversione);C5605;fabbrica (SMT)
C9;100nF;C_0603_1608Metric;CC0603KRX7R9BB104 50V;C14663;fabbrica (SMT)
R20;10k;R_0603_1608Metric;0603WAF1002T5E;C25804;fabbrica (SMT)
R21;10k;R_0603_1608Metric;0603WAF1002T5E;C25804;fabbrica (SMT)
R22;10k;R_0603_1608Metric;0603WAF1002T5E;C25804;fabbrica (SMT)
U4;74HCT245;SOIC-20W_7.5x12.8mm_P1.27mm;74HCT245D,653 (ingressi TTL, uscite 5V);C5979;fabbrica (SMT)
C6;100nF;C_0603_1608Metric;CC0603KRX7R9BB104 50V;C14663;fabbrica (SMT)
R23;100;R_0603_1608Metric;0603WAF1000T5E;C22775;fabbrica (SMT)
R24;100;R_0603_1608Metric;0603WAF1000T5E;C22775;fabbrica (SMT)
R25;100;R_0603_1608Metric;0603WAF1000T5E;C22775;fabbrica (SMT)
R26;1k;R_0603_1608Metric;0603WAF1001T5E;C21190;fabbrica (SMT)
D6;PUL giallo;LED_0603_1608Metric;KT-0603Y;C2287;fabbrica (SMT)
R27;1k;R_0603_1608Metric;0603WAF1001T5E;C21190;fabbrica (SMT)
D7;DIR giallo;LED_0603_1608Metric;KT-0603Y;C2287;fabbrica (SMT)
R28;1k;R_0603_1608Metric;0603WAF1001T5E;C21190;fabbrica (SMT)
D8;ENA rosso;LED_0603_1608Metric;KT-0603R;C2286;fabbrica (SMT)
J3;TB6600;TerminalBlock_Phoenix_MKDS-1,5-5-5.08_1x05_P5.08mm_Horizontal;PUL->PUL+, DIR->DIR+, ENA->ENA+, GND->PUL-/DIR-/ENA-, +5V solo per anodo comune;;a mano (THT)
J5;RAZORGAUGE;TerminalBlock_Phoenix_MKDS-1,5-8-5.08_1x08_P5.08mm_Horizontal;cavo schermato max 50 cm, calza al pin 8;;a mano (THT)
R40;100;R_0603_1608Metric;0603WAF1000T5E;C22775;fabbrica (SMT)
R41;100;R_0603_1608Metric;0603WAF1000T5E;C22775;fabbrica (SMT)
R42;100;R_0603_1608Metric;0603WAF1000T5E;C22775;fabbrica (SMT)
C10;1nF;C_0603_1608Metric;CL10B102KB8NNNC 50V;C1588;fabbrica (SMT)
D9;1N4148W;D_SOD-123;1N4148W;C81598;fabbrica (SMT)
D10;1N4148W;D_SOD-123;1N4148W;C81598;fabbrica (SMT)
C11;10uF 25V;C_0805_2012Metric;CL21A106KAYNNNE;C15850;fabbrica (SMT)
C12;100nF;C_0603_1608Metric;CC0603KRX7R9BB104 50V;C14663;fabbrica (SMT)
JP2;SEL LASER;PinHeader_1x03_P2.54mm_Vertical;Header 3 pin + jumper (1-2 = laser a 3.3V, 2-3 = laser a 5V);;a mano (THT)
R43;0;R_0603_1608Metric;0603WAF0000T5E;C21189;fabbrica (SMT)
Q1;2N7002;SOT-23;2N7002 (60V 115mA);C8545;fabbrica (SMT)
R44;100;R_0603_1608Metric;0603WAF1000T5E;C22775;fabbrica (SMT)
R45;100k;R_0603_1608Metric;0603WAF1003T5E;C25803;fabbrica (SMT)
SW1;SCAN;SW_PUSH_6mm;;;a mano (THT)
R52;10k;R_0603_1608Metric;0603WAF1002T5E;C25804;fabbrica (SMT)
R53;1k;R_0603_1608Metric;0603WAF1001T5E;C21190;fabbrica (SMT)
C14;100nF;C_0603_1608Metric;CC0603KRX7R9BB104 50V;C14663;fabbrica (SMT)
SW2;FAST_S;SW_PUSH_6mm;;;a mano (THT)
R54;10k;R_0603_1608Metric;0603WAF1002T5E;C25804;fabbrica (SMT)
R55;1k;R_0603_1608Metric;0603WAF1001T5E;C21190;fabbrica (SMT)
C15;100nF;C_0603_1608Metric;CC0603KRX7R9BB104 50V;C14663;fabbrica (SMT)
SW3;FAST_O;SW_PUSH_6mm;;;a mano (THT)
R56;10k;R_0603_1608Metric;0603WAF1002T5E;C25804;fabbrica (SMT)
R57;1k;R_0603_1608Metric;0603WAF1001T5E;C21190;fabbrica (SMT)
C16;100nF;C_0603_1608Metric;CC0603KRX7R9BB104 50V;C14663;fabbrica (SMT)
SW4;WIFI_RST;SW_PUSH_6mm;;;a mano (THT)
R50;10k;R_0603_1608Metric;0603WAF1002T5E;C25804;fabbrica (SMT)
R51;1k;R_0603_1608Metric;0603WAF1001T5E;C21190;fabbrica (SMT)
C13;100nF;C_0603_1608Metric;CC0603KRX7R9BB104 50V;C14663;fabbrica (SMT)
J6;PULSANTI;TerminalBlock_Phoenix_MKDS-1,5-5-5.08_1x05_P5.08mm_Horizontal;;;a mano (THT)
H1;M3;MountingHole_3.2mm_M3_Pad;;;a mano (THT)
H2;M3;MountingHole_3.2mm_M3_Pad;;;a mano (THT)
H3;M3;MountingHole_3.2mm_M3_Pad;;;a mano (THT)
H4;M3;MountingHole_3.2mm_M3_Pad;;;a mano (THT)

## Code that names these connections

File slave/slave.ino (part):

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#define PUL_PIN 25     // era 4 (S3)
#define DIR_PIN 26     // era 5
#define ENA_PIN 27     // era 6
#define BTN_SCAN 32    // era 10
#define BTN_FAST_S 33  // era 11
#define BTN_FAST_O 34  // era 12 — GPIO34 e solo ingresso, senza pull-up interna: la pull-up 10k e sulla scheda
#define UART_RX 16     // era 21 — RX2, collegato al TX2 (GPIO17) del master
#define UART_TX 17     // era 18 — TX2, collegato al RX2 (GPIO16) del master

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  SerialMaster.begin(115200, SERIAL_8N1, UART_RX, UART_TX);
  
  // Configura pulsanti
  pinMode(BTN_SCAN, INPUT_PULLUP);
  pinMode(BTN_FAST_S, INPUT_PULLUP);
  pinMode(BTN_FAST_O, INPUT);         // GPIO34: solo ingresso, nessuna pull-up interna (evita l'errore di pinMode); pull-up 10k sulla scheda
  
  // Inizializza stepper
  engine.init();
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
